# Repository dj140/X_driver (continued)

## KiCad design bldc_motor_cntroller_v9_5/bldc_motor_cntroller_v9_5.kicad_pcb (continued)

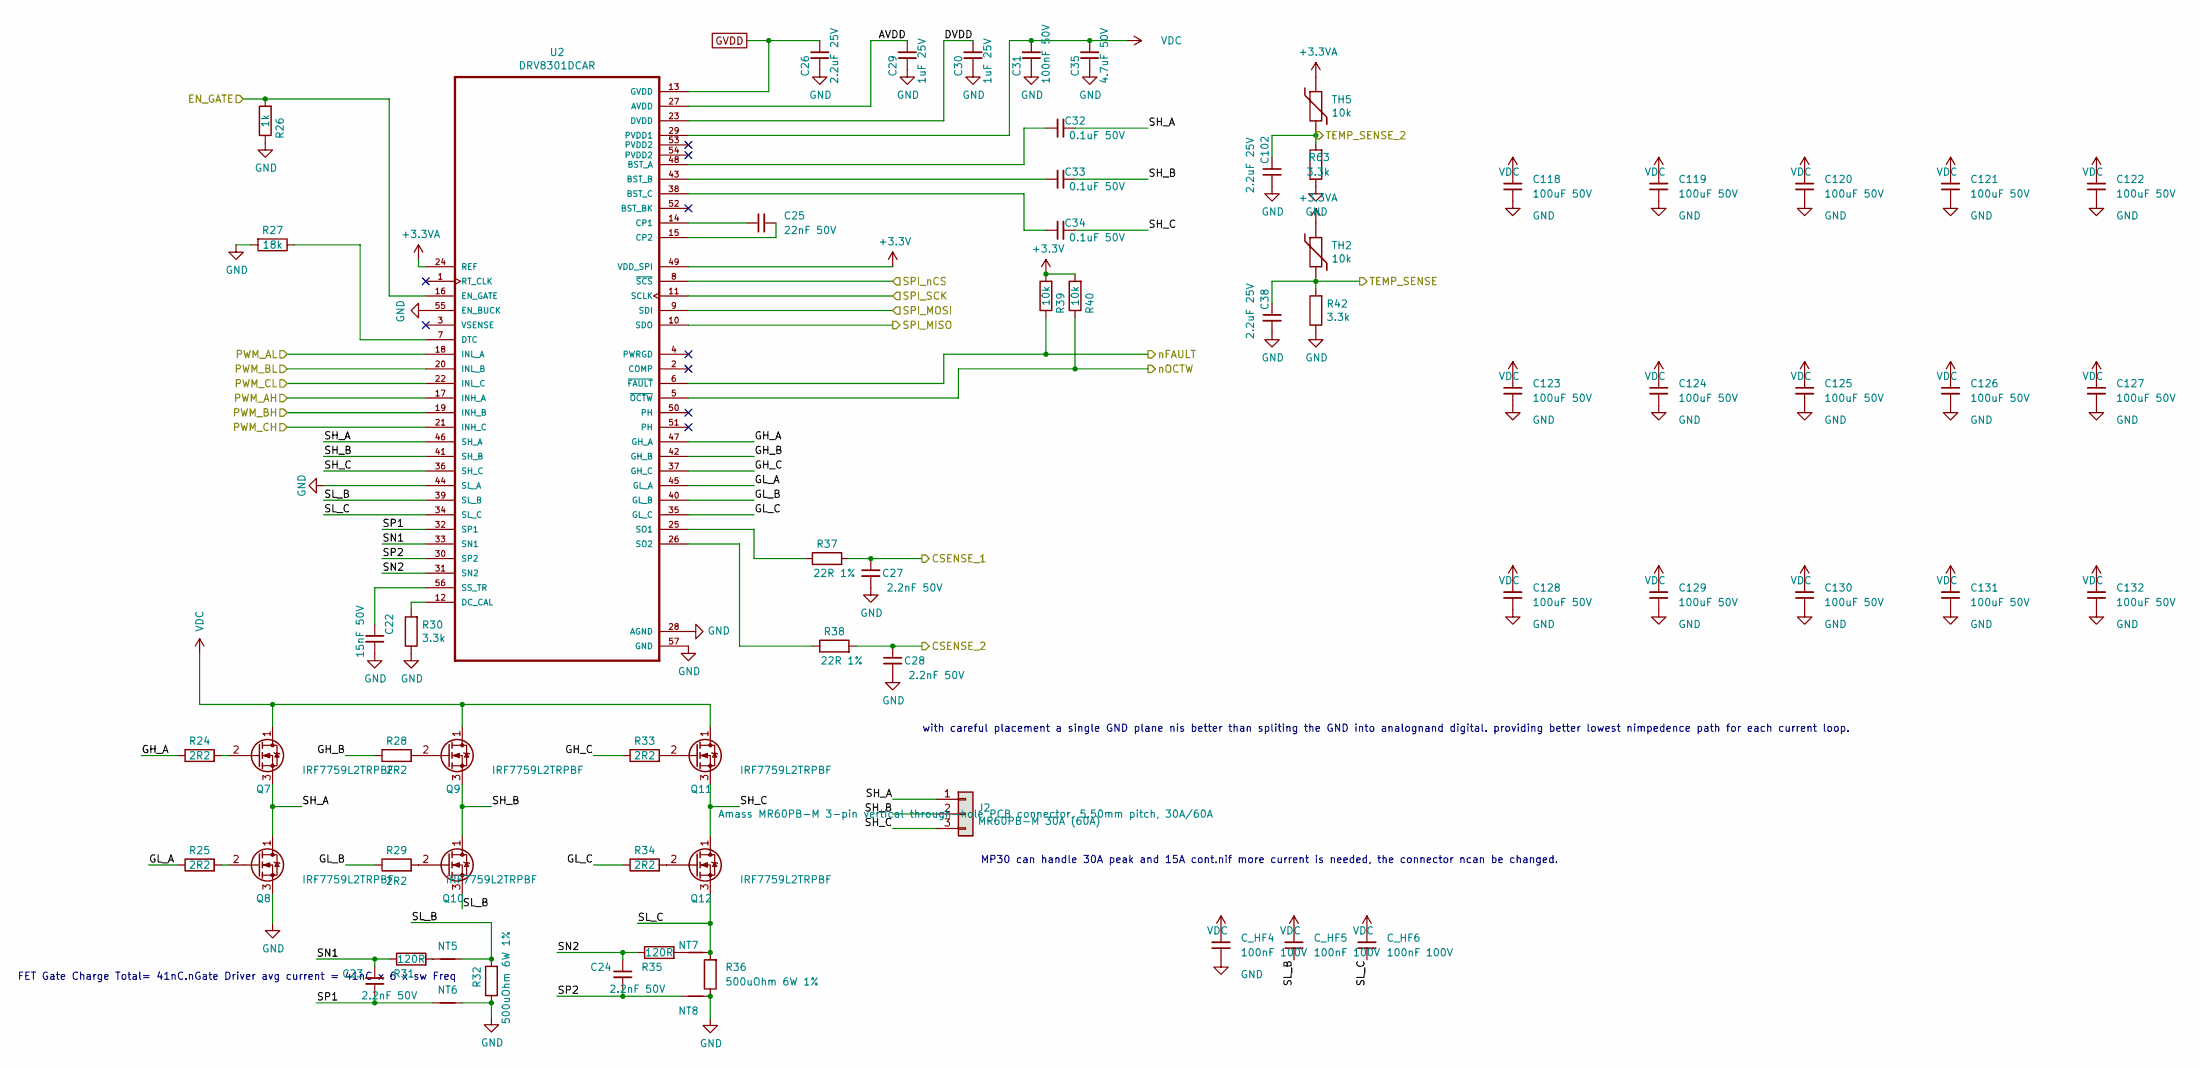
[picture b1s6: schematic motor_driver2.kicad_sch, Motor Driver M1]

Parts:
C22: 15nF 50V; C_0402_1005Metric; MPN GCM155R71E153JA55D
C23, C24, C27, C28: 2.2nF 50V; C_0402_1005Metric; MPN C0402C222J3GEC7411; LCSC Part # C1531
C25: 22nF 50V; C_0402_1005Metric; MPN C0402C223K5REC7411; LCSC Part # C1532
C26, C38, C102: 2.2uF 25V; C_0402_1005Metric; MPN GRM155C81E225KE11D; LCSC Part # C12530
C29, C30: 1uF 25V; C_0402_1005Metric; MPN GMK105CC6105MV-F; LCSC Part # C52923
C31: 100nF 50V; C_0402_1005Metric; MPN GRM155R62A104KE14D
C32, C33, C34: 0.1uF 50V; C_0402_1005Metric; MPN GCM155L8EH104KE07D
C35: 4.7uF 50V; C_1206_3216Metric; MPN HMK325C7475KN-TE
C118, C119, C120, C121, C122, C123, C124, C125, C126, C127, C128, C129, C130, C131, C132: 100uF 50V; C_1206_3216Metric; MPN GMK105CC6105MV-F
C_HF4, C_HF5, C_HF6: 100nF 100V; C_0603_1608Metric; MPN GCM188R72A104KA64D
J2: MR60PB-M 30A (60A); AMASS_MR60PB-M_1x03_P5.50mm_Vertical; MPN MR60PB-M
NT5, NT6, NT7, NT8: Net-Tie_2; NetTie-2_SMD_Pad0.5mm
Q7, Q8, Q9, Q10, Q11, Q12: IRF7759L2TRPBF; DirectFET_L8; MPN IRF7759L2TRPBF; LCSC C520641
R24, R25, R28, R29, R33, R34: 2R2; R_0402_1005Metric; MPN CRCW04022R20FKEDC
R26: 1k; R_0402_1005Metric; MPN ERJ-2RKF1001X; LCSC Part # C11702
R27: 18k; R_0402_1005Metric; MPN CRCW040218K0FKED; LCSC Part # C25762
R30, R42, R63: 3.3k; R_0402_1005Metric; MPN CRCW04023K30FKEDC; LCSC Part # C25890
R31, R35: 120R; R_0402_1005Metric; MPN ERJ-2RKF1200X; LCSC Part # C25079
R32, R36: 500uOhm 6W 1%; R_2512_6332Metric; MPN CSS2H-2512R-L500F
R37, R38: 22R 1%; R_0402_1005Metric; MPN CRCW040222R0FKEDC; LCSC Part # C25092
R39, R40: 10k; R_0402_1005Metric; MPN CRCW040210K0FKEDC; LCSC Part # C25744
TH2, TH5: 10k; R_0402_1005Metric; MPN CRCW040210K0FKEDC
U2: DRV8301DCAR; DRV8301DCA_v9; MPN DRV8301DCAR

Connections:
+3.3V: R39.2, R40.2, U2.49 (VDD_SPI); also elsewhere on the board
+3.3VA: TH2.1, TH5.1, U2.24 (REF); also elsewhere on the board
/Microcontroller Interface/EN_GATE: R26.2, U2.16 (EN_GATE); also elsewhere on the board
/Microcontroller Interface/M1_AH: U2.17 (INH_A); also elsewhere on the board
/Microcontroller Interface/M1_AL: U2.18 (INL_A); also elsewhere on the board
/Microcontroller Interface/M1_BH: U2.19 (INH_B); also elsewhere on the board
/Microcontroller Interface/M1_BL: U2.20 (INL_B); also elsewhere on the board
/Microcontroller Interface/M1_CH: U2.21 (INH_C); also elsewhere on the board
/Microcontroller Interface/M1_CL: U2.22 (INL_C); also elsewhere on the board
/Microcontroller Interface/M1_SO1: C27.2, R37.2; also elsewhere on the board
/Microcontroller Interface/M1_SO2: C28.2, R38.2; also elsewhere on the board
/Microcontroller Interface/M1_TEMP: C38.1, R42.2, TH2.2; also elsewhere on the board
/Microcontroller Interface/SPI_M1_nCS: U2.8 (~SCS); also elsewhere on the board
/Microcontroller Interface/SPI_MISO: U2.10 (SDO); also elsewhere on the board
/Microcontroller Interface/SPI_MOSI: U2.9 (SDI); also elsewhere on the board
/Microcontroller Interface/SPI_SCK: U2.11 (SCLK); also elsewhere on the board
/Microcontroller Interface/nFAULT: R39.1, U2.6 (~FAULT); also elsewhere on the board
/Motor_Driver2/AVDD: C29.1, U2.27 (AVDD)
/Motor_Driver2/DVDD: C30.1, U2.23 (DVDD)
/Motor_Driver2/GH_A: R24.1, U2.47 (GH_A)
/Motor_Driver2/GH_B: R28.1, U2.42 (GH_B)
/Motor_Driver2/GH_C: R33.1, U2.37 (GH_C)
/Motor_Driver2/GL_A: R25.1, U2.45 (GL_A)
/Motor_Driver2/GL_B: R29.1, U2.40 (GL_B)
/Motor_Driver2/GL_C: R34.1, U2.35 (GL_C)
/Motor_Driver2/SH_A: C32.1, J2.1, Q7.3 (S), Q8.1 (D), U2.46 (SH_A)
/Motor_Driver2/SH_B: C33.1, J2.2, Q9.3 (S), Q10.1 (D), U2.41 (SH_B)
/Motor_Driver2/SH_C: C34.1, J2.3, Q11.3 (S), Q12.1 (D), U2.36 (SH_C)
/Motor_Driver2/SL_B: C_HF5.2, NT5.2, Q10.3 (S), R32.2, U2.39 (SL_B)
/Motor_Driver2/SL_C: C_HF6.2, NT7.2, Q12.3 (S), R36.2, U2.34 (SL_C)
/Motor_Driver2/SN1: C23.2, R31.1, U2.33 (SN1)
/Motor_Driver2/SN2: C24.2, R35.1, U2.31 (SN2)
/Motor_Driver2/SP1: C23.1, NT6.1, U2.32 (SP1)
/Motor_Driver2/SP2: C24.1, NT8.1, U2.30 (SP2)
/Motor_Driver2/TEMP_SENSE_2: C102.1, R63.2, TH5.2
/Motor_Driver2/nOCTW: R40.1, U2.5 (~OCTW)
GND: C22.1, C26.2, C27.1, C28.1, C29.2, C30.2, C31.2, C35.2, C38.2, C102.2, C118.2, C119.2, C120.2, C121.2, C122.2, C123.2, C124.2, C125.2, C126.2, C127.2, C128.2, C129.2, C130.2, C131.2, C132.2, C_HF4.2, NT6.2, NT8.2, Q8.3 (S), R26.1, R27.2, R30.1, R32.1, R36.1, R42.1, R63.1, U2.28 (AGND), U2.44 (SL_A), U2.55 (EN_BUCK), U2.57 (GND); also elsewhere on the board
GVDD: C26.1, U2.13 (GVDD); also elsewhere on the board
unnamed: NT5.1, R31.2
unnamed: NT7.1, R35.2
unnamed: Q7.2 (G), R24.2
unnamed: Q8.2 (G), R25.2
unnamed: Q9.2 (G), R28.2
unnamed: Q10.2 (G), R29.2
unnamed: Q11.2 (G), R33.2
unnamed: Q12.2 (G), R34.2
unnamed: C32.2, U2.48 (BST_A)
unnamed: C33.2, U2.43 (BST_B)
unnamed: C34.2, U2.38 (BST_C)
unnamed: C25.1, U2.14 (CP1)
unnamed: C25.2, U2.15 (CP2)
unnamed: R30.2, U2.12 (DC_CAL)
unnamed: R27.1, U2.7 (DTC)
unnamed: R37.1, U2.25 (SO1)
unnamed: R38.1, U2.26 (SO2)
unnamed: C22.2, U2.56 (SS_TR)
VDC: C31.1, C35.1, C118.1, C119.1, C120.1, C121.1, C122.1, C123.1, C124.1, C125.1, C126.1, C127.1, C128.1, C129.1, C130.1, C131.1, C132.1, C_HF4.1, C_HF5.1, C_HF6.1, Q7.1 (D), Q9.1 (D), Q11.1 (D), U2.29 (PVDD1); also elsewhere on the board

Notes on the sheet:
FET Gate Charge Total= 41nC.nGate Driver avg current = 41nC x 6 x sw Freq
MP30 can handle 30A peak and 15A cont.nif more current is needed, the connector ncan be changed.
with careful placement a single GND plane nis better than spliting the GND into analognand digital. providing better lowest nimpedence path for each current loop.

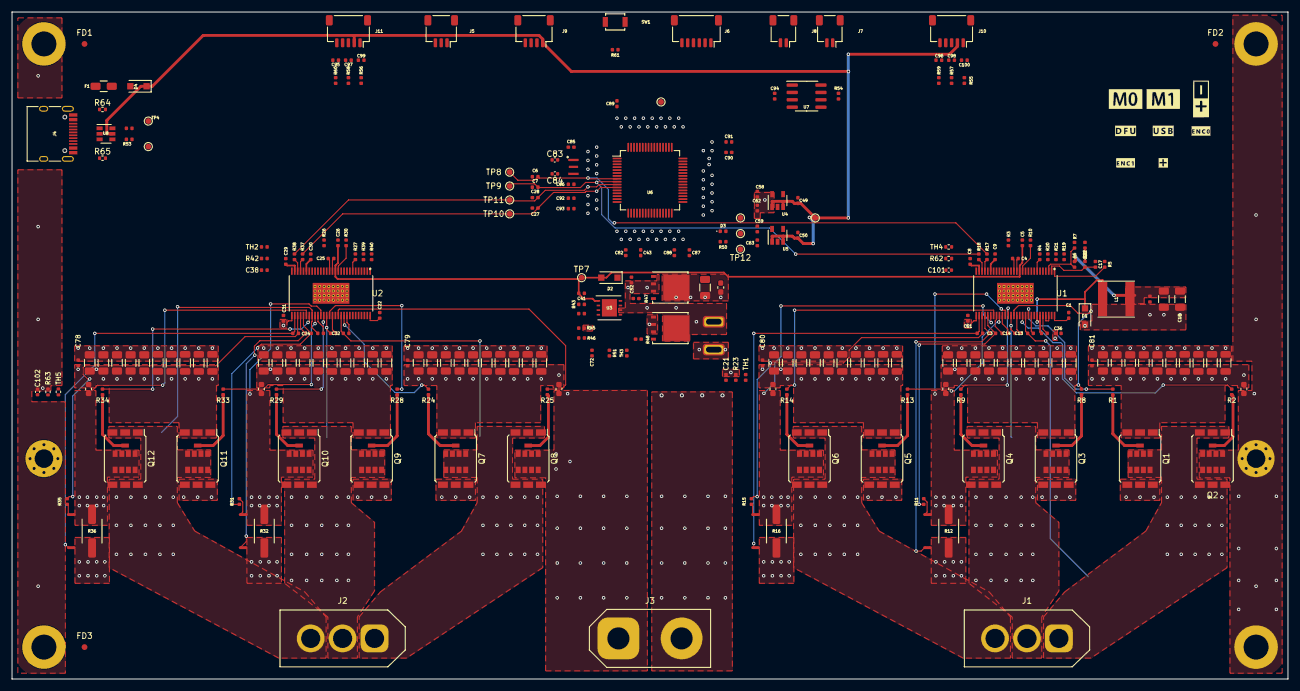
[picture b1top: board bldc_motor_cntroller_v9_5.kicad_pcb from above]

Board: 4 copper layers, 220.0 x 115.0 mm, 286 parts (0 on the bottom side), 157 nets.

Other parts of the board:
G1: LOGO; M00
G2: LOGO; M1
G3: LOGO; batt
G4: LOGO; DFU
G5: LOGO; USB
G6: LOGO; ENC0
G7: LOGO; ENC1
G8: LOGO; ++

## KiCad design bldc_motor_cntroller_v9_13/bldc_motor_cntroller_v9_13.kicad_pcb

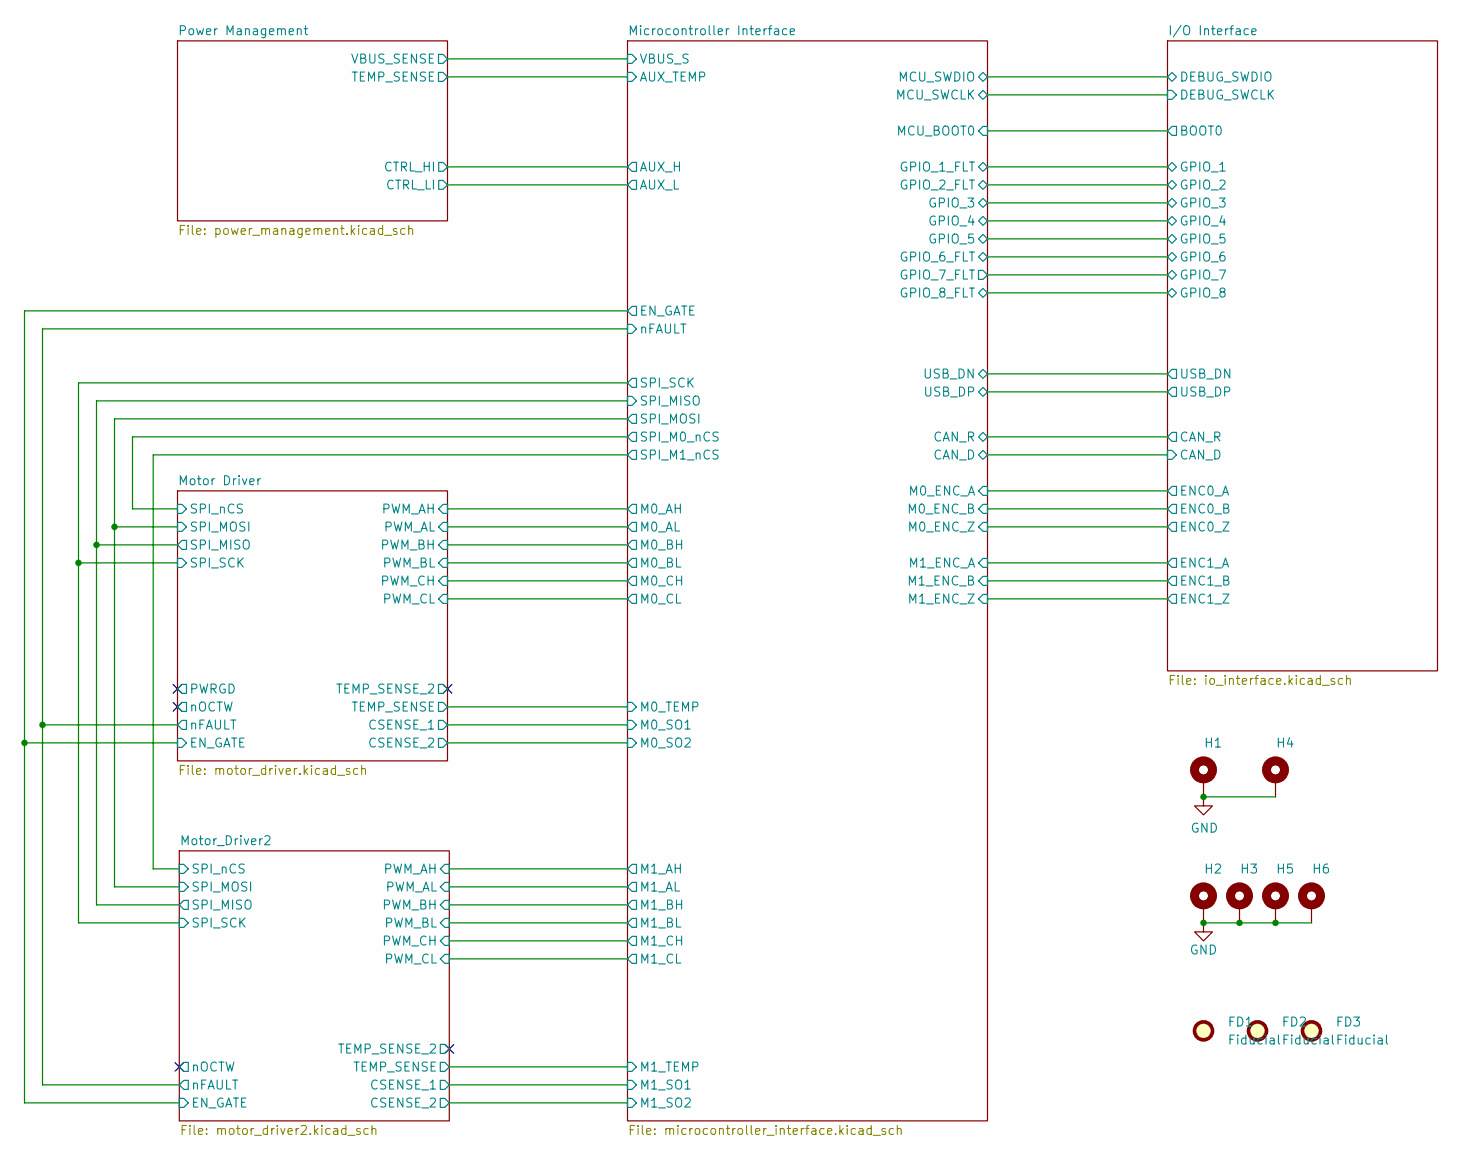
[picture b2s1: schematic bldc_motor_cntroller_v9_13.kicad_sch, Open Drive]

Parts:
FD1, FD2, FD3: Fiducial; Fiducial_1mm_Mask2mm
H1, H4: MountingHole_3.2mm_M3_Pad_Via
H2, H3, H5, H6: MountingHole_Pad; MountingHole_4.3mm_M4_Pad

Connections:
GND: H1.1 (1_1), H2.1 (1_1), H3.1 (1_1), H4.1 (1_1), H5.1 (1_1), H6.1 (1_1); also elsewhere on the board

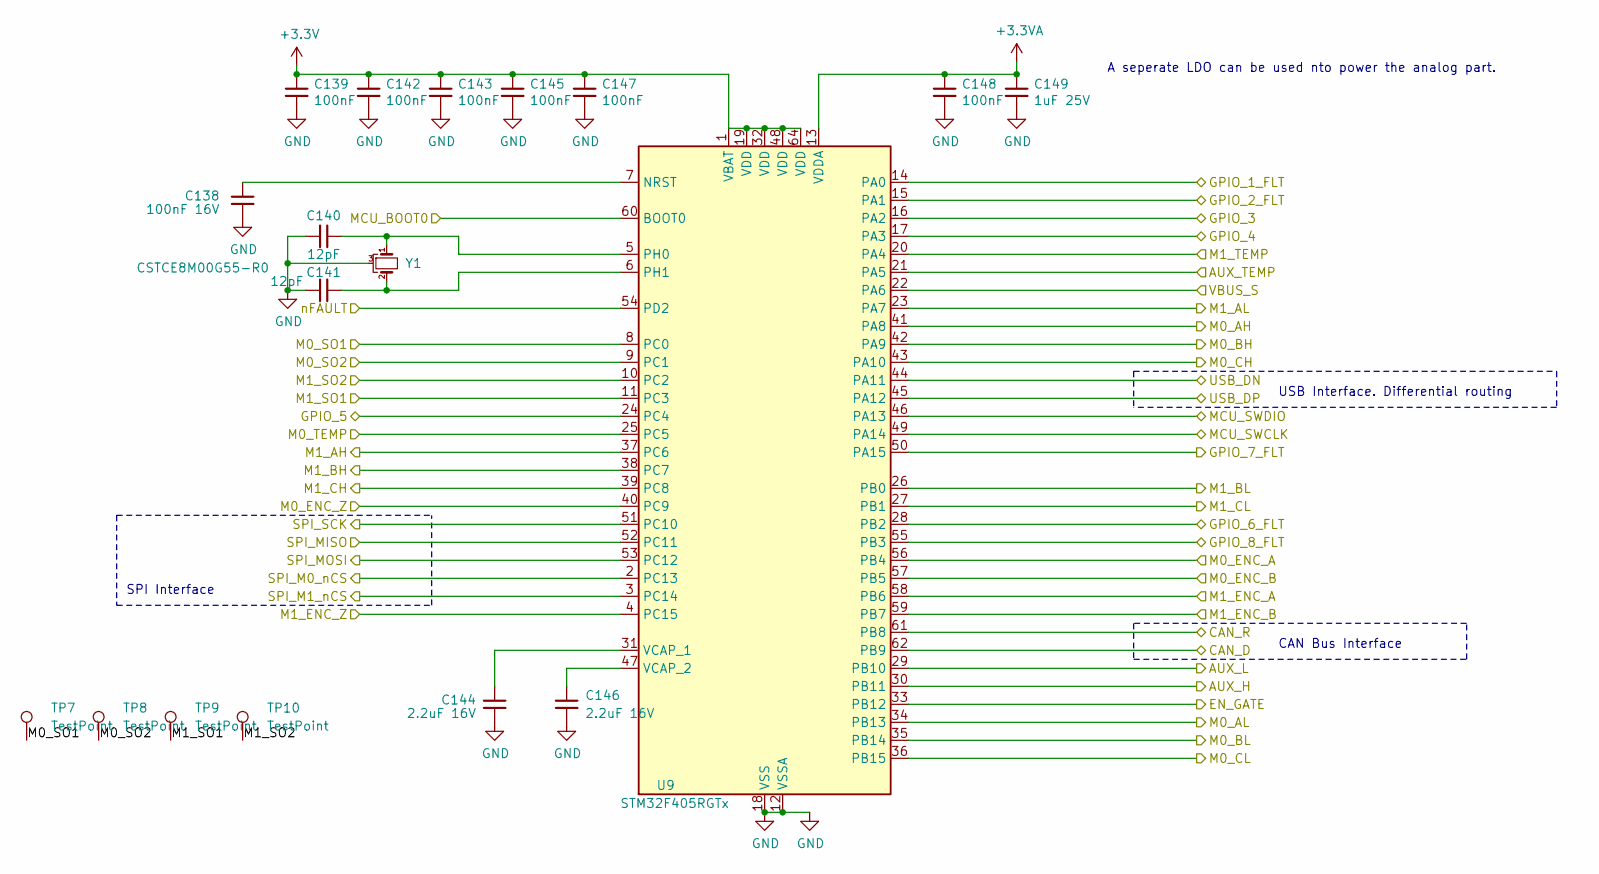
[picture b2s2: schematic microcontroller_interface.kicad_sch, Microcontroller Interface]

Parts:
C138: 100nF 16V; C_0402_1005Metric; MPN GRM155C81E225KE11D; LCSC Part # C1525
C139, C142, C143, C145, C147, C148: 100nF; C_0402_1005Metric; MPN GRM155R62A104KE14D; LCSC Part # C1525
C140, C141: 12pF; C_0402_1005Metric; MPN GCQ1555C1H120FB01D; LCSC Part # C1547
C144, C146: 2.2uF 16V; C_0402_1005Metric; MPN GRM155C81E225KE11D
C149: 1uF 25V; C_0402_1005Metric; MPN GMK105CC6105MV-F; LCSC Part # C52923
TP7, TP8, TP9, TP10: TestPoint; TestPoint_Pad_D1.0mm
U9: STM32F405RGTx; LQFP-64_10x10mm_P0.5mm; MPN STM32F405RGT7
Y1: CSTCE8M00G55-R0; MPN CSTCE8M00G55-R0

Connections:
+3.3V: C139.1, C142.1, C143.1, C145.1, C147.1, U9.1 (VBAT), U9.19 (VDD), U9.32 (VDD), U9.48 (VDD), U9.64 (VDD); also elsewhere on the board
+3.3VA: C148.1, C149.1, U9.13 (VDDA); also elsewhere on the board
/I/O Interface/BOOT0: U9.60 (BOOT0); also elsewhere on the board
/I/O Interface/CAN_D: U9.62 (PB9); also elsewhere on the board
/I/O Interface/CAN_R: U9.61 (PB8); also elsewhere on the board
/I/O Interface/DEBUG_SWCLK: U9.49 (PA14); also elsewhere on the board
/I/O Interface/DEBUG_SWDIO: U9.46 (PA13); also elsewhere on the board
/I/O Interface/ENC0_A: U9.56 (PB4); also elsewhere on the board
/I/O Interface/ENC0_B: U9.57 (PB5); also elsewhere on the board
/I/O Interface/ENC0_Z: U9.40 (PC9); also elsewhere on the board
/I/O Interface/ENC1_A: U9.58 (PB6); also elsewhere on the board
/I/O Interface/ENC1_B: U9.59 (PB7); also elsewhere on the board
/I/O Interface/ENC1_Z: U9.4 (PC15); also elsewhere on the board
/I/O Interface/GPIO_1: U9.14 (PA0); also elsewhere on the board
/I/O Interface/GPIO_2: U9.15 (PA1); also elsewhere on the board
/I/O Interface/GPIO_3: U9.16 (PA2); also elsewhere on the board
/I/O Interface/GPIO_4: U9.17 (PA3); also elsewhere on the board
/I/O Interface/GPIO_5: U9.24 (PC4); also elsewhere on the board
/I/O Interface/GPIO_6: U9.28 (PB2); also elsewhere on the board
/I/O Interface/GPIO_7: U9.50 (PA15); also elsewhere on the board
/I/O Interface/GPIO_8: U9.55 (PB3); also elsewhere on the board
/I/O Interface/USB_DN: U9.44 (PA11); also elsewhere on the board
/I/O Interface/USB_DP: U9.45 (PA12); also elsewhere on the board
/Microcontroller Interface/AUX_TEMP: U9.21 (PA5); also elsewhere on the board
/Microcontroller Interface/EN_GATE: U9.33 (PB12); also elsewhere on the board
/Microcontroller Interface/M0_AH: U9.41 (PA8); also elsewhere on the board
/Microcontroller Interface/M0_AL: U9.34 (PB13); also elsewhere on the board
/Microcontroller Interface/M0_BH: U9.42 (PA9); also elsewhere on the board
/Microcontroller Interface/M0_BL: U9.35 (PB14); also elsewhere on the board
/Microcontroller Interface/M0_CH: U9.43 (PA10); also elsewhere on the board
/Microcontroller Interface/M0_CL: U9.36 (PB15); also elsewhere on the board
/Microcontroller Interface/M0_SO1: TP7.1, U9.8 (PC0); also elsewhere on the board
/Microcontroller Interface/M0_SO2: TP8.1, U9.9 (PC1); also elsewhere on the board
/Microcontroller Interface/M0_TEMP: U9.25 (PC5); also elsewhere on the board
/Microcontroller Interface/M1_AH: U9.37 (PC6); also elsewhere on the board
/Microcontroller Interface/M1_AL: U9.23 (PA7); also elsewhere on the board
/Microcontroller Interface/M1_BH: U9.38 (PC7); also elsewhere on the board
/Microcontroller Interface/M1_BL: U9.26 (PB0); also elsewhere on the board
/Microcontroller Interface/M1_CH: U9.39 (PC8); also elsewhere on the board
/Microcontroller Interface/M1_CL: U9.27 (PB1); also elsewhere on the board
/Microcontroller Interface/M1_SO1: TP9.1, U9.11 (PC3); also elsewhere on the board
/Microcontroller Interface/M1_SO2: TP10.1, U9.10 (PC2); also elsewhere on the board
/Microcontroller Interface/M1_TEMP: U9.20 (PA4); also elsewhere on the board
/Microcontroller Interface/SPI_M0_nCS: U9.2 (PC13); also elsewhere on the board
/Microcontroller Interface/SPI_M1_nCS: U9.3 (PC14); also elsewhere on the board
/Microcontroller Interface/SPI_MISO: U9.52 (PC11); also elsewhere on the board
/Microcontroller Interface/SPI_MOSI: U9.53 (PC12); also elsewhere on the board
/Microcontroller Interface/SPI_SCK: U9.51 (PC10); also elsewhere on the board
/Microcontroller Interface/VBUS_S: U9.22 (PA6); also elsewhere on the board
/Microcontroller Interface/nFAULT: U9.54 (PD2); also elsewhere on the board
GND: C138.2, C139.2, C140.1, C141.1, C142.2, C143.2, C144.2, C145.2, C146.2, C147.2, C148.2, C149.2, U9.12 (VSSA), U9.18 (VSS), U9.63 (VSS), Y1.3; also elsewhere on the board
unnamed: C138.1, U9.7 (NRST)
unnamed: C140.2, U9.5 (PH0), Y1.1
unnamed: C141.2, U9.6 (PH1), Y1.2
unnamed: C144.1, U9.31 (VCAP_1)
unnamed: C146.1, U9.47 (VCAP_2)
OVP_IN_HI: U9.30 (PB11); also elsewhere on the board
OVP_IN_LI: U9.29 (PB10); also elsewhere on the board

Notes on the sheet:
CAN Bus Interface
USB Interface. Differential routing
SPI Interface
A seperate LDO can be used nto power the analog part.

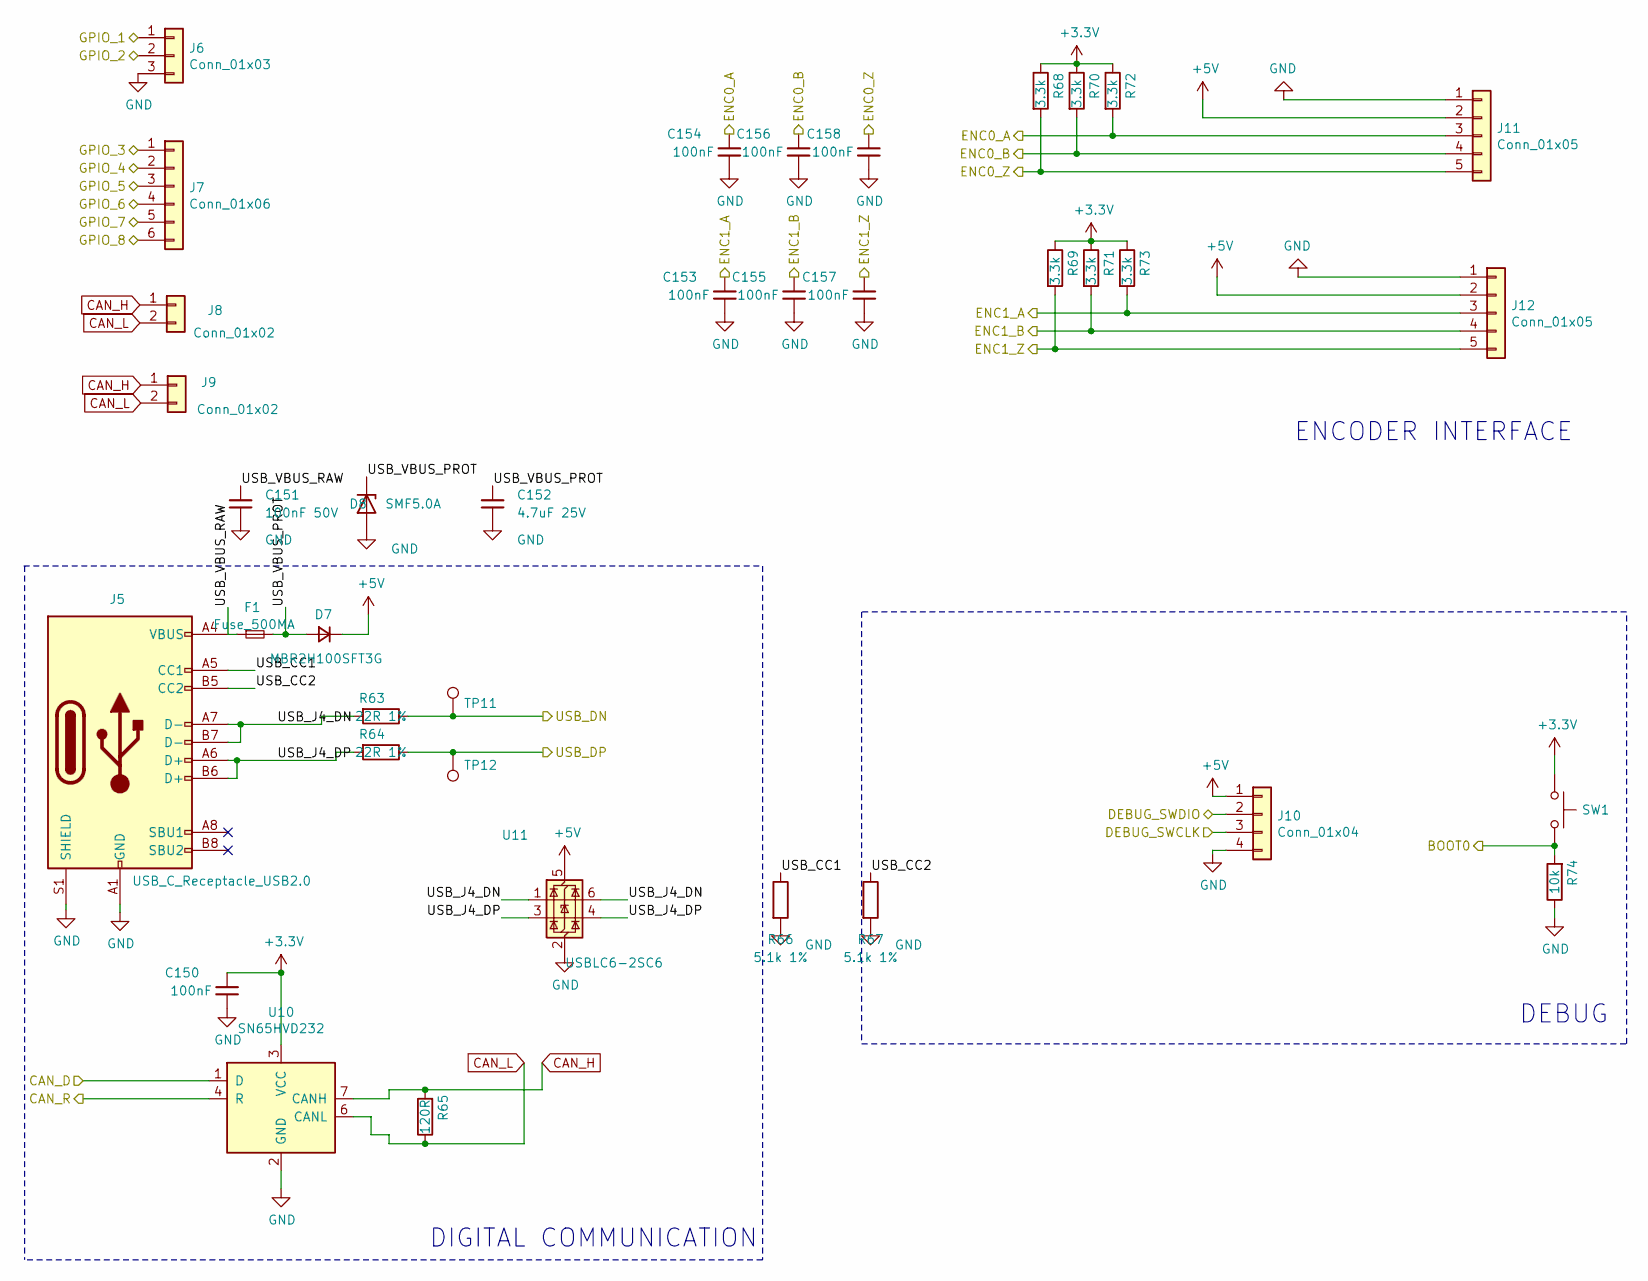
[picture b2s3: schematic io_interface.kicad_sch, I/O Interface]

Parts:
C150, C153, C154, C155, C156, C157, C158: 100nF; C_0402_1005Metric; MPN GRM155R62A104KE14D; LCSC Part # C1525
C151: 100nF 50V; C_0402_1005Metric; MPN CC0402KRX7R9BB104; LCSC C131394
C152: 4.7uF 25V; C_0805_2012Metric; MPN CL21B475KAB6PNE; LCSC C16194942
D7: MBR2H100SFT3G; D_SOD-123F
D8: SMF5.0A; D_SOD-123F; MPN SMF5.0A; LCSC C2857263
F1: Fuse_500MA; Fuse_1206_3216Metric
J5: USB_C_Receptacle_USB2.0; USB_C_Receptacle_HRO_TYPE-C-31-M-12
J6: Conn_01x03; JST_SH_SM03B-SRSS-TB_1x03-1MP_P1.00mm_Horizontal
J7: Conn_01x06; JST_SH_SM06B-SRSS-TB_1x06-1MP_P1.00mm_Horizontal
J8, J9: Conn_01x02; JST_SH_SM02B-SRSS-TB_1x02-1MP_P1.00mm_Horizontal
J10: Conn_01x04; JST_SH_SM04B-SRSS-TB_1x04-1MP_P1.00mm_Horizontal
J11, J12: Conn_01x05; JST_SH_SM05B-SRSS-TB_1x05-1MP_P1.00mm_Horizontal
R63, R64: 22R 1%; R_0402_1005Metric; MPN CRCW040222R0FKEDC; LCSC Part # C25092
R65: 120R; R_0402_1005Metric; MPN ERJ-2RKF1200X; LCSC Part # C25079
R66, R67: 5.1k 1%; R_0402_1005Metric; MPN CRCW04025K10FKED
R68, R69, R70, R71, R72, R73: 3.3k; R_0402_1005Metric; MPN CRCW04023K30FKEDC; LCSC Part # C25890
R74: 10k; R_0402_1005Metric; MPN CRCW040210K0FKEDC; LCSC Part # C25744
SW1: B3U-1000P-B; SW_SPST_B3U-1000P; MPN B3U-1000P-B
TP11, TP12: TestPoint; TestPoint_Pad_D1.0mm
U10: SN65HVD232; SOIC-8_3.9x4.9mm_P1.27mm
U11: USBLC6-2SC6; SOT-23-6

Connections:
+3.3V: C150.2, R68.1, R69.1, R70.1, R71.1, R72.1, R73.1, SW1.1, U10.3 (VCC); also elsewhere on the board
+5V: D7.1 (K), J10.1, J11.2, J12.2, U11.5 (VBUS); also elsewhere on the board
/I/O Interface/BOOT0: R74.2, SW1.2; also elsewhere on the board
/I/O Interface/CAN_D: U10.1 (D); also elsewhere on the board
/I/O Interface/CAN_R: U10.4 (R); also elsewhere on the board
/I/O Interface/DEBUG_SWCLK: J10.3; also elsewhere on the board
/I/O Interface/DEBUG_SWDIO: J10.2; also elsewhere on the board
/I/O Interface/ENC0_A: C154.2, J11.3, R72.2; also elsewhere on the board
/I/O Interface/ENC0_B: C156.2, J11.4, R70.2; also elsewhere on the board
/I/O Interface/ENC0_Z: C158.2, J11.5, R68.2; also elsewhere on the board
/I/O Interface/ENC1_A: C153.2, J12.3, R73.2; also elsewhere on the board
/I/O Interface/ENC1_B: C155.2, J12.4, R71.2; also elsewhere on the board
/I/O Interface/ENC1_Z: C157.2, J12.5, R69.2; also elsewhere on the board
/I/O Interface/GPIO_1: J6.1; also elsewhere on the board
/I/O Interface/GPIO_2: J6.2; also elsewhere on the board
/I/O Interface/GPIO_3: J7.1; also elsewhere on the board
/I/O Interface/GPIO_4: J7.2; also elsewhere on the board
/I/O Interface/GPIO_5: J7.3; also elsewhere on the board
/I/O Interface/GPIO_6: J7.4; also elsewhere on the board
/I/O Interface/GPIO_7: J7.5; also elsewhere on the board
/I/O Interface/GPIO_8: J7.6; also elsewhere on the board
/I/O Interface/USB_CC1: J5.A5 (CC1), R66.1
/I/O Interface/USB_CC2: J5.B5 (CC2), R67.1
/I/O Interface/USB_DN: R63.1, TP11.1; also elsewhere on the board
/I/O Interface/USB_DP: R64.1, TP12.1; also elsewhere on the board
/I/O Interface/USB_J4_DN: J5.A7 (D-), J5.B7 (D-), R63.2, U11.1 (I/O1), U11.6 (I/O1)
/I/O Interface/USB_J4_DP: J5.A6 (D+), J5.B6 (D+), R64.2, U11.3 (I/O2), U11.4 (I/O2)
/I/O Interface/USB_VBUS_PROT: C152.1, D7.2 (A), D8.1 (K), F1.2
/I/O Interface/USB_VBUS_RAW: C151.1, F1.1, J5.A4 (VBUS), J5.A9 (VBUS), J5.B4 (VBUS), J5.B9 (VBUS)
CAN_H: J8.1, J9.1, R65.2, U10.7 (CANH)
CAN_L: J8.2, J9.2, R65.1, U10.6 (CANL)
GND: C150.1, C151.2, C152.2, C153.1, C154.1, C155.1, C156.1, C157.1, C158.1, D8.2 (A), J5.A1 (GND), J5.A12 (GND), J5.B1 (GND), J5.B12 (GND), J5.S1 (SHIELD), J6.3, J10.4, J11.1, J12.1, R66.2, R67.2, R74.1, U10.2 (GND), U11.2 (GND); also elsewhere on the board

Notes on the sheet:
DIGITAL COMMUNICATION
ENCODER INTERFACE
DEBUG

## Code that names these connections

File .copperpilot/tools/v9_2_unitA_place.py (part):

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placements["U1"] = (U1_X, U1_Y, -90.0)

# South of U2 (pins at y = 72.32):
#   pin 29 (-6.75=48.25): VDC -> C31 (100nF) at (46.80, 72.80, 90)
#   pins 30,31 (-6.25,-5.75 = 48.75,49.25): SP2,SN2 -> C24 at (48.90, 75.40, 0)
#   pins 32,33 (-5.25,-4.75 = 49.75,50.25): SP1,SN1 -> C23 at (50.80, 75.40, 0)
#   pins 36,38 (-3.25,-2.25 = 51.75,52.75): SH_C,BST_C -> C34 at (52.75, 75.40, 0)
#   pins 41,43 (-0.75,+0.25 = 54.25,55.25): SH_B,BST_B -> C33 at (55.25, 75.40, 0)
#   pins 46,48 (+1.75,+2.75 = 56.75,57.75): SH_A,BST_A -> C32 at (57.75, 75.40, 0)
#   pin 56 (+6.75=61.75): SS_TR -> C22 at (63.40, 72.30, -90 -> Pad 2 SS_TR North, Pad 1 GND South)
placements.update({
    "C31": (U2_X - 8.20, 72.80,  90.0),
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    "C22": (U2_X + 8.40, 72.30, -90.0),

    # North of U2 (pins at y = 64.68):
    #   pin 27 (-6.25=48.75): AVDD -> C29 at (47.20, 63.00, 90)
    #   pins 25,26 (-5.25,-5.75 = 49.75,49.25): SO1,SO2 -> R37(50.0, 62.2, 90), R38(48.6, 62.2, 90)
    #   pin 23 (-4.25=50.75): DVDD -> C30 at (51.40, 62.20, 90)
    #   pin 16 (-0.75=54.25): EN_GATE -> R26 at (53.80, 60.20, -90)
    #   pins 14,15 (+0.25,-0.25 = 55.25,54.75): CP1,CP2 -> C25 at (55.00, 62.50, 180)
    #   pin 13 (+0.75=55.75): GVDD -> C26 at (56.20, 60.20, 90)
    #   pin 12 (+1.25=56.25): DC_CAL -> R30 at (57.60, 60.20, -90)
    #   pin 7  (+3.75=58.75): DTC -> R27 at (59.20, 62.20, 90)
    #   pins 6,5 (+4.25,+4.75 = 59.25,59.75): nFAULT, nOCTW -> R39(60.6, 62.2, 90), R40(62.0, 62.2, 90)
    "C29": (U2_X - 7.80, 63.00,  90.0),
    "R38": (U2_X - 6.30, 62.20,  90.0),
    "R37": (U2_X - 4.90, 62.20,  90.0),
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    "C15": (U1_X - 1.80, 75.40,   0.0),
    "C14": (U1_X + 0.40, 75.40,   0.0),
    "C13": (U1_X + 2.60, 75.40,   0.0),
    # Pins 50,51 (+3.75,+4.25=176.75,177.25): PH (Net-(D1-K)); Pin 52 (+4.75=177.75): BST_BK; Pins 53,54 (+5.25,+5.75=178.25,178.75): PVDD2(VDC); Pin 56 (+6.75=179.75): SS_TR
    "C10": (U1_X + 5.00, 75.40,   0.0),   # BST_BK <-> Net-(D1-K), right below pins 50-52!
    "C36": (U1_X + 7.40, 75.40,   0.0),   # VDC <-> GND, right below pins 53-54!
    "C1":  (U1_X + 9.20, 72.30, -90.0),   # SS_TR <-> GND, right beside pin 56!

    # East-side Buck Power Stage (right next to PH pins 50-51 at x=177.0, y=72.32!):
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# --- Central Brake Chopper (U3 LM5109B, Q13, Q14, H5, H6) centered at x = 104..122, y = 61..73 ---
# Look how clean this is:
#   U3 at (103.0, 66.0, rot=0):
#     West pins (101.1): 1=GVDD, 2=AUX_H, 3=AUX_L, 4=GND
#     East pins (104.9): 8=Net-(D2-K) (y=64.8), 7=HO (y=65.6), 6=HS (y=66.4), 5=LO (y=67.2)
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#   And Q13 at (113.5, 62.5, rot=0) + Q14 at (113.5, 69.5, rot=0):
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placements.update({
    # West side of U6 (pins 1..16 at x = 104.33, y = 40.25..47.75):
    "C85": (100.20, 39.80, 180.0),      # +3.3V(East) <-> GND(West) for pin 1 (40.25)
    "Y1":  ( 99.80, 42.50, -90.0),      # PH0(41.3), GND(42.5), PH1(43.7) right opposite pins 5,6 (42.25, 42.75)!
    "C83": ( 96.80, 41.20,   0.0),      # GND(West) <-> PH0(East)
    "C84": ( 96.80, 43.80,   0.0),      # GND(West) <-> PH1(East)
    "C86": ( 96.80, 39.20, 180.0),      # NRST(East) <-> GND(West)
    "C92": (100.20, 46.25, 180.0),      # +3.3VA(East) <-> GND(West) for pin 13 (46.25)
    "C93": (100.20, 48.00, 180.0),      # +3.3VA(East) <-> GND(West)

    # ADC SO1/SO2 filter caps & spaced TestPoints (no silk overlap!):
    "C6":   ( 93.50, 43.75,   0.0),     # GND(West) <-> M0_SO1(East -> pin 8 at 43.75)
    "C7":   ( 93.50, 45.25,   0.0),     # GND(West) <-> M0_SO2(East -> pin 9 at 44.25)
    "C28":  ( 93.50, 46.75,   0.0),     # GND(West) <-> M1_SO2(East -> pin 10 at 44.75)
    "C27":  ( 93.50, 48.25,   0.0),     # GND(West) <-> M1_SO1(East -> pin 11 at 45.25)
    "TP8":  ( 88.50, 42.50,   0.0),
    "TP9":  ( 88.50, 45.50,   0.0),
    "TP11": ( 88.50, 48.50,   0.0),
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
    # South side of U6 (pins 17..32 at y = 49.67, x = 106.25..113.75):
    "C82": (107.25, 53.20, -90.0),      # +3.3V(North) <-> GND(South) for pin 19
    "C43": (109.25, 53.20, -90.0),      # VBUS_S(North) <-> GND(South) for pin 22
    "C88": (112.75, 53.20, -90.0),      # VCAP_1(North) <-> GND(South) for pin 31
    "C87": (114.75, 53.20, -90.0),      # +3.3V(North) <-> GND(South) for pin 32
    "D3":  (118.50, 52.20,   0.0),      # +3.3V LED
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
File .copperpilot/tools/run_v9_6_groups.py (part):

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        "/Microcontroller Interface/AUX_L",
    ], 10, 95, None, None, [], []),
    "s_gpio6_s": ([
        "/I{slash}O Interface/GPIO_6",
    ], 10, 105, None, None, ["118.15,20.40,120.85,23.60", "107.70,50.70,110.30,52.00"], []),
    "s_m0temp_g": ([
        "/Microcontroller Interface/M0_TEMP",
    ], 10, 95, None, None, ["107.70,50.70,109.80,52.00"], []),
    "s_gpio5_s": ([
        "/I{slash}O Interface/GPIO_5",
    ], 10, 105, None, None, ["119.15,20.40,120.85,23.60", "107.70,50.70,109.30,52.00"], []),
    "s_m1al_g": ([
        "/Microcontroller Interface/M1_AL",
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        "107.60,54.75,109.48,56.50",
    ], ["109.30,50.65,110.70,54.92"]),
    "sa_gpio5_left": ([
        "/I{slash}O Interface/GPIO_5",
    ], 12, 115, None, None, [
        "107.60,50.65,108.82,54.45",
        "119.15,20.40,120.85,23.60",
    ], []),
    "pair_gpio5_m0temp": ([
        "/I{slash}O Interface/GPIO_5",
        "/Microcontroller Interface/M0_TEMP",
    ], 14, 135, None, None, [
        "107.60,50.65,108.82,54.55",
        "119.15,20.40,120.85,23.60",
    ], ["109.30,50.65,110.70,53.95"]),
    "sb_gpio6_via": ([
        "/I{slash}O Interface/GPIO_6",
    ], 12, 115, None, None, [
        "107.60,50.65,108.82,54.45",
        "112.10,50.65,114.50,59.95",
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        "/Microcontroller Interface/AUX_H",
    ], 10, 100, None, None, [], ["106.00,50.65,114.50,61.05"]),
    "trio_b": ([
        "/I{slash}O Interface/GPIO_6",
        "/Microcontroller Interface/AUX_L",
        "/Microcontroller Interface/AUX_H",
    ], 16, 165, None, None, [
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        "118.15,20.40,120.85,23.60",
    ], ["111.30,50.65,114.50,58.50"]),
    "pair_gpio56": ([
        "/I{slash}O Interface/GPIO_5",
        "/I{slash}O Interface/GPIO_6",
    ], 14, 140, None, None, [
        "107.60,50.65,108.82,54.45",
        "110.22,50.65,110.65,53.50",
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        "119.15,20.40,120.85,23.60",
    ], ["109.20,50.65,116.50,58.50"]),
    "sa_gpio5": ([
        "/I{slash}O Interface/GPIO_5",
    ], 12, 115, None, None, [
        "107.60,50.65,108.82,54.45",
        "110.22,50.65,110.65,53.50",
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        "109.45,54.15,110.10,54.82",
    ], ["109.30,50.65,110.70,54.85"]),
    "sb_gpio6": ([
        "/I{slash}O Interface/GPIO_6",
    ], 10, 105, None, None, [
        "107.60,50.65,108.82,54.45",
        "109.20,55.60,111.42,57.60",
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    ], ["107.50,50.65,109.20,53.45"]),
    "pa_3": ([
        "/Microcontroller Interface/M1_AL",
        "/I{slash}O Interface/GPIO_5",
        "/Microcontroller Interface/M0_TEMP",
    ], 14, 140, None, None, [
        "108.10,50.65,108.82,55.55",
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        "94.00,59.40,94.30,59.90",
    ], []),
    "pb_3": ([
        "/I{slash}O Interface/GPIO_6",
        "/Microcontroller Interface/AUX_L",
        "/Microcontroller Interface/AUX_H",
    ], 14, 140, None, None, [
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        "94.00,59.40,94.30,59.90",
    ], ["108.85,51.00,110.75,55.40"]),
    "g5_gpio5": ([
        "/I{slash}O Interface/GPIO_5",
    ], 12, 115, None, None, [
        "109.95,50.65,113.05,54.35",
        "119.15,20.40,120.85,23.60",
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        "/Microcontroller Interface/M0_TEMP",
    ], 10, 95, None, None, ["111.60,50.65,113.05,51.65"], []),
    "g7_gpio6": ([
        "/I{slash}O Interface/GPIO_6",
    ], 10, 105, None, None, ["112.15,50.65,113.05,54.50", "118.15,20.40,120.85,23.60"], []),
    "g8_auxl": ([
        "/Microcontroller Interface/AUX_L",
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        "/Microcontroller Interface/M0_TEMP",
    ], 10, 95, None, None, ["108.00,50.70,109.90,56.80"], ["108.00,50.70,109.90,56.80"]),
    "r_gpio5": ([
        "/I{slash}O Interface/GPIO_5",
    ], 12, 115, None, None, ["108.00,50.70,109.40,56.80", "119.15,20.40,120.85,23.60"], ["108.00,50.70,109.40,56.80"]),
    "r_m1al": ([
        "/Microcontroller Interface/M1_AL",
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        "90.00,51.48,90.30,51.90",
    ], ["109.70,51.00,110.50,57.30"]),
    "l_gpio5": ([
        "/I{slash}O Interface/GPIO_5",
    ], 12, 115, None, None, ["110.30,52.30,110.55,57.30", "119.15,20.40,120.85,23.60"], ["110.20,51.00,110.55,57.30"]),
    "l_m0temp": ([
        "/Microcontroller Interface/M0_TEMP",
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        "/I{slash}O Interface/DEBUG_SWDIO",
    ], 10, 105, None, None, ["88.20,20.40,89.80,22.80", "115.20,20.60,120.80,23.20"]),
    "gpio78_first": ([
        "/I{slash}O Interface/GPIO_7",
        "/I{slash}O Interface/GPIO_8",
    ], 10, 105, None, None, ["117.20,20.60,120.80,23.20"]),
    "s_swclk": ([
        "/I{slash}O Interface/DEBUG_SWCLK",
    ], 10, 105, None, None, ["117.20,20.60,120.80,23.20"]),
    "swclk_gpio78": ([
        "/I{slash}O Interface/DEBUG_SWCLK",
        "/I{slash}O Interface/GPIO_7",
        "/I{slash}O Interface/GPIO_8",
    ], 12, 135, None, None, ["117.20,20.60,120.80,23.20"]),
    "swd_gpio78": ([
        "/I{slash}O Interface/DEBUG_SWCLK",
        "/I{slash}O Interface/DEBUG_SWDIO",
        "/I{slash}O Interface/GPIO_7",
        "/I{slash}O Interface/GPIO_8",
    ], 12, 135, None, None, ["117.20,20.60,120.80,23.20"]),
    "s_gpio6": ([
        "/I{slash}O Interface/GPIO_6",
    ], 10, 105, None, None, ["118.15,20.40,120.85,23.60"]),
    "s_gpio5": ([
        "/I{slash}O Interface/GPIO_5",
    ], 10, 105, None, None, ["119.15,20.40,120.85,23.60"]),
    "s_gpio4": ([
        "/I{slash}O Interface/GPIO_4",
    ], 10, 105, None, None, ["120.15,20.40,120.85,23.60"]),
    "s_gpio3": ([
        "/I{slash}O Interface/GPIO_3",
    ], 10, 105, None, None),
    "j6_gpio3456": ([
        "/I{slash}O Interface/GPIO_3",
        "/I{slash}O Interface/GPIO_4",
        "/I{slash}O Interface/GPIO_5",
        "/I{slash}O Interface/GPIO_6",
    ], 14, 150, None, None, ["109.05,49.80,109.45,52.60", "110.55,49.80,111.45,52.60"]),
    "west_gpio12": ([
        "/I{slash}O Interface/GPIO_1",
        "/I{slash}O Interface/GPIO_2",
    ], 10, 105, None, None),
    "south_left4": ([
        "/I{slash}O Interface/GPIO_4",
        "/Microcontroller Interface/M1_TEMP",
        "/Microcontroller Interface/AUX_TEMP",
        "/Microcontroller Interface/VBUS_S",
    ], 12, 140, None, None, ["110.55,49.80,111.45,52.80"]),
    "south_right5": ([
        "/I{slash}O Interface/GPIO_5",
        "/Microcontroller Interface/M0_TEMP",
        "/I{slash}O Interface/GPIO_6",
        "/Microcontroller Interface/AUX_L",
        "/Microcontroller Interface/AUX_H",
    ], 12, 150, None, None, ["110.55,49.80,111.45,52.80"]),
    "north_j6_j9_chute": ([
        "/I{slash}O Interface/GPIO_7",
        "/I{slash}O Interface/GPIO_8",
        "/I{slash}O Interface/DEBUG_SWCLK",
        "/I{slash}O Interface/DEBUG_SWDIO",
    ], 12, 140, None, None, ["111.05,35.40,112.95,38.20"]),
    "west_gpio123": ([
        "/I{slash}O Interface/GPIO_1",
        "/I{slash}O Interface/GPIO_2",
        "/I{slash}O Interface/GPIO_3",
    ], 10, 120, None, None),
    "m1_re5_clean": ([
        "/Microcontroller Interface/M1_AL",
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        "/Microcontroller Interface/M1_TEMP",
    ], 14, 150, None, None),
    "north_j6_j9": ([
        "/I{slash}O Interface/GPIO_7",
        "/I{slash}O Interface/GPIO_8",
        "/I{slash}O Interface/DEBUG_SWCLK",
        "/I{slash}O Interface/DEBUG_SWDIO",
    ], 14, 150, None, None),
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        "/Microcontroller Interface/nFAULT",
    ], 10, 105, None),
    "b7a_gpio78": ([
        "/I{slash}O Interface/GPIO_7",
        "/I{slash}O Interface/GPIO_8",
    ], 8, 85, None),
    "b7b_gpio56": ([
        "/I{slash}O Interface/GPIO_5",
        "/I{slash}O Interface/GPIO_6",
    ], 8, 85, None),
    "b7c_gpio34": ([
        "/I{slash}O Interface/GPIO_3",
        "/I{slash}O Interface/GPIO_4",
    ], 8, 85, None),
    "b7d_gpio12": ([
        "/I{slash}O Interface/GPIO_1",
        "/I{slash}O Interface/GPIO_2",
    ], 8, 85, None),
    "enc0z_only": ([
        "/I{slash}O Interface/ENC0_Z",
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
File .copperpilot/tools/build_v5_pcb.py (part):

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
    # West pin-adjacent caps (C85->U6.1, C88->U6.5, C90->U6.6, C86->U6.7, C92/C93->U6.12/13 VDDA/VSSA)
    ("C85", 66.50, 41.00, 0),     # +3.3V U6.1 (2.3 mm)
    ("C88", 66.50, 42.60, 0),     # Net-(U6-PH0) U6.5 (2.3 mm, was 11.1 mm!)
    ("C90", 66.50, 44.10, 0),     # Net-(U6-PH1) U6.6 (2.3 mm, was 14.7 mm!)
    ("C86", 66.50, 45.60, 0),     # NRST U6.7 (2.6 mm, was 8.7 mm!)
    ("C92", 63.40, 47.25, -90),   # 100nF +3.3VA at VDDA/VSSA (was 9.5 mm on SE!)
    ("C93", 61.20, 47.25, -90),   # 1uF +3.3VA at VDDA/VSSA (was 11.5 mm on SE!)

    # Resonator Y1 + C83 + C84 at SW corner clear of U6 courtyard (x_right = 67.85 < 68.30!)
    ("Y1",  66.50, 50.40, -90),
    ("C83", 66.50, 47.50, 180),   # Net-(U6-PC3) -> 2.6 mm from U6.11!
    ("C84", 69.80, 53.20, 180),   # Net-(U6-PC4) -> 5.1 mm from U6.24 (was 12.1 mm!)

    # North, East, South VDD decoupling + ADC anti-aliasing filter caps right at U6 ADC pins!
    ("C89", 71.25, 36.80, -90),   # +3.3V U6.64 (2.0 mm)
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    pose_map[ref] = (round(cx - 70.00, 3), 81.45, 90)

# Shunts under west SL exits at y = 96.90 mm (rot = 180), side-by-side differential NT + 120R launch at y = 94.55 mm
# keeping SL_C & SL_B 100% single-piece unobstructed!
for ref, x, y, rot in [
    ("R16", 92.60, 97.20, 180),    # Pad2 SL_C=(89.70,97.20), Pad1 GND=(95.50,97.20 -> x_right=96.18!)
    ("NT3", 92.15, 94.35, 180),    # Pad2 SL_C=(91.65,94.35) inside SL_C; Pad1=(92.65,94.35)
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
